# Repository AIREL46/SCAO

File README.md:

# SCAO
Système de Cuisson Assistée par Ordinateur
Ce système est décrit sur le site fablabo http://fablabo.net/wiki/SCAO
Les fichiers de ce projet, au fur et à mesure de l'avancement,  permettent la fabrication des différents sous-ensembles du prototype N°3.

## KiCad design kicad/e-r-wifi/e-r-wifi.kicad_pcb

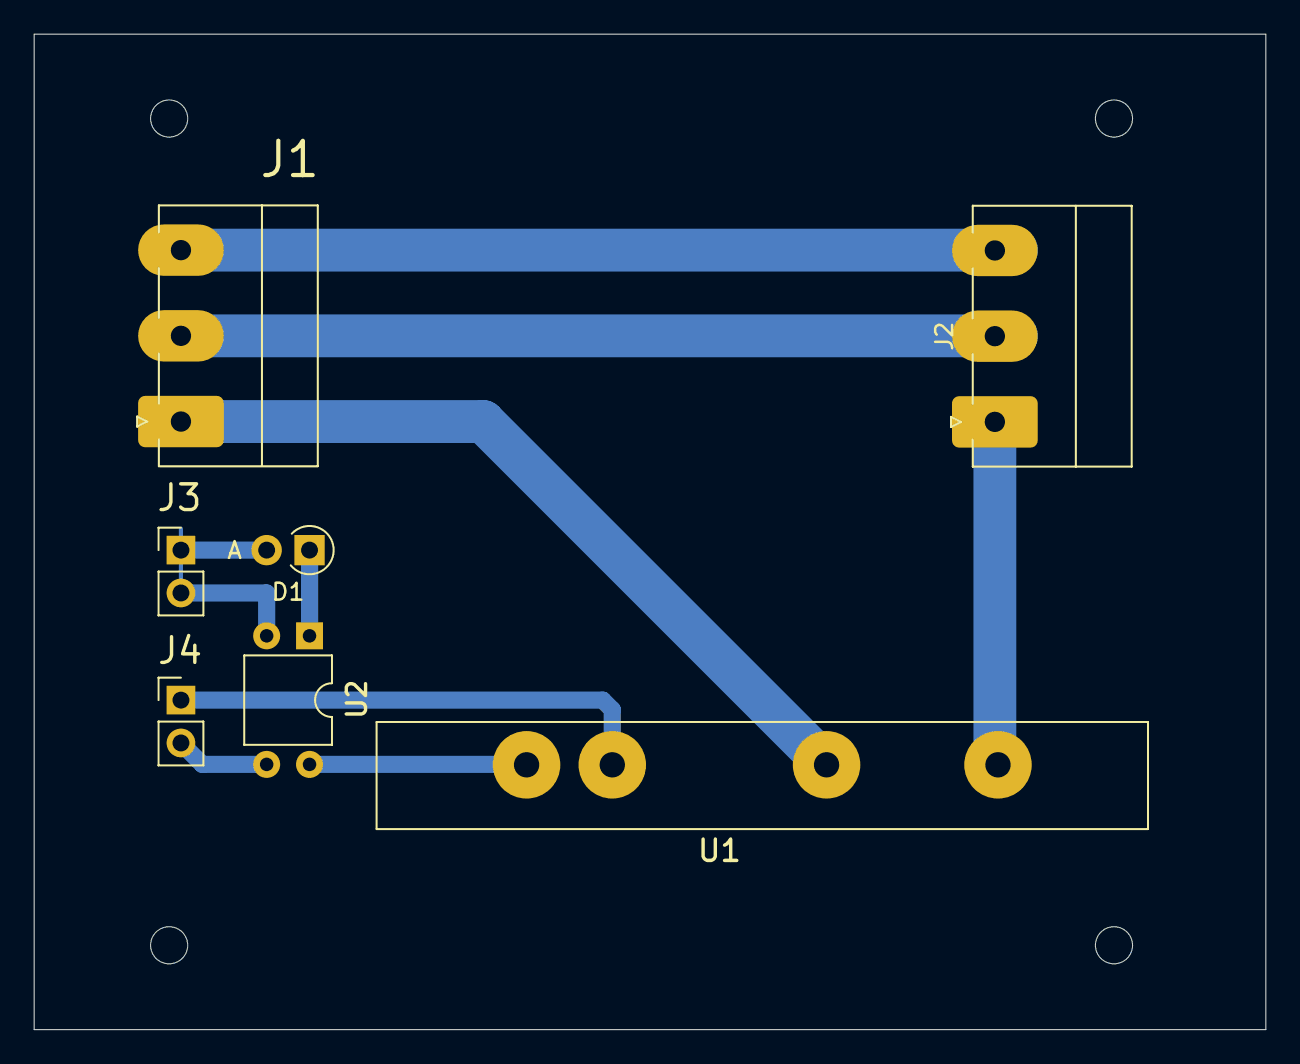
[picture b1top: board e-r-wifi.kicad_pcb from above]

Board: 2 copper layers, 73.0 x 59.0 mm, 7 parts (0 on the bottom side), 9 nets.

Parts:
D1: LED; D_A-405_P2.54mm_Vertical_AnodeUp
J1: Entrée 230V; PhoenixContact_MC_1,5_3-G-5.08_1x03_P5.08mm_Horizontal
J2: Sortie 230V; PhoenixContact_MC_1,5_3-G-5.08_1x03_P5.08mm_Horizontal
J3: cde relais Celduc; PinHeader_1x02_P2.54mm_Vertical
J4: 5V; PinHeader_1x02_P2.54mm_Vertical
U1: SKL10120
U2: PC817; DIP-4_W7.62mm

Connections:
GND: J4.2, U2.3
unnamed: D1.1, U2.1
unnamed: D1.2, J3.1, J3.2, U2.2
unnamed: J1.1, U1.2
unnamed: J1.2, J2.2
unnamed: J1.3, J2.3
unnamed: J2.1, U1.1
unnamed: J4.1, U1.3
unnamed: U1.4, U2.4

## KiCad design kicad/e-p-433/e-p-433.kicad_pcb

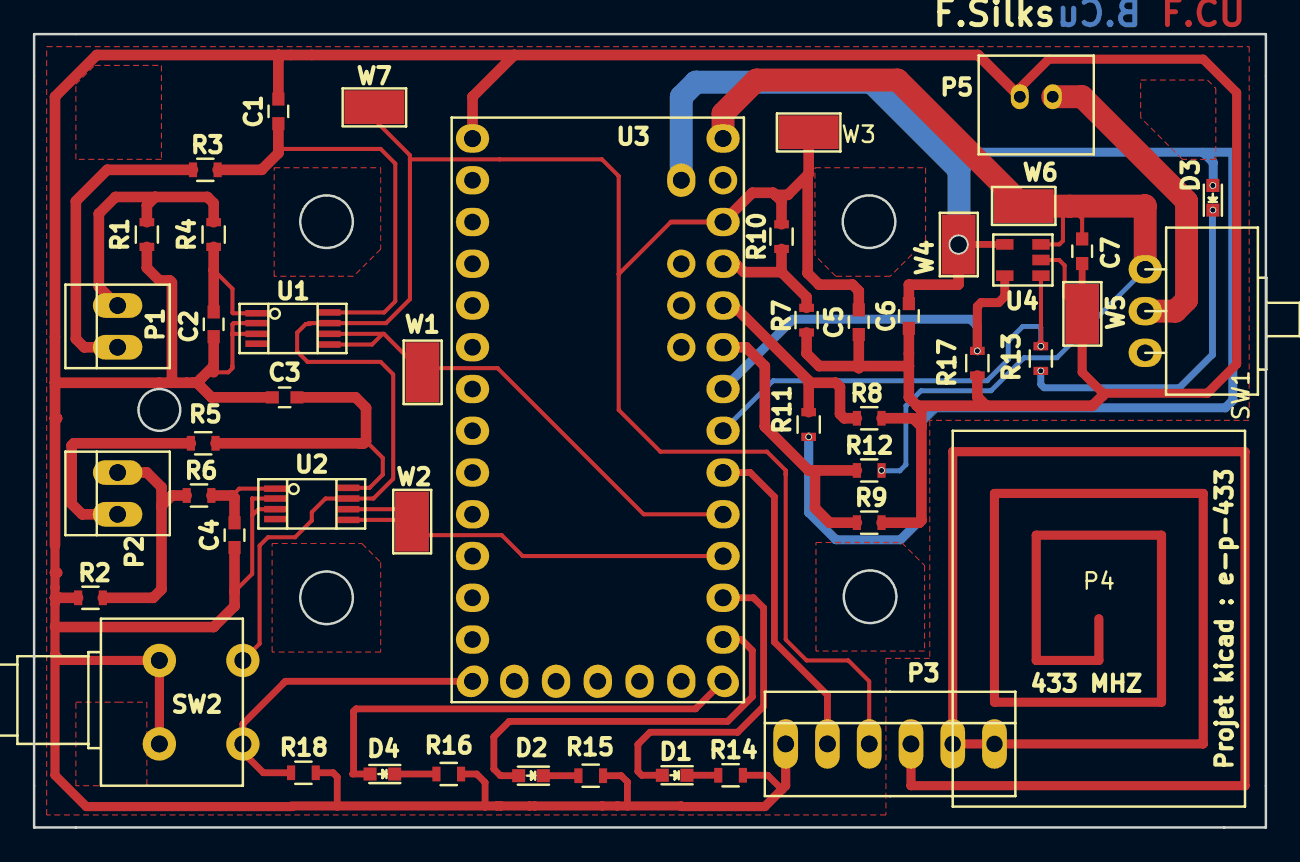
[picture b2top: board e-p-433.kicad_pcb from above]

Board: 2 copper layers, 74.9 x 48.3 mm, 48 parts (0 on the bottom side), 30 nets.

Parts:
C1, C2, C3, C4: 0.1µF; C_0603
C5, C6, C7: 4.7µF; C_0603
D1: Rouge; LED_0603
D2, D3: Jaune; LED_0603
D4: Verte; LED_0603
P1, P2: CONN_01X02; PINHEAD1-2
P3: Transmitter; PINHEAD1-6
P4: ant; Ant
P5: Batterie; con_bat
R1, R2: 1M; R_0603
R3, R4, R5, R6: 10K; R_0603
R7, R8, R9, R10, R11, R12, R17: 4.7K; R_0603
R13: 470; R_0603
R14, R15, R16: 1K; R_0603
R18: 47K; R_0603
SW1: SWITCH_INV; SW_Micro_SPST_Angled
SW2: SW_PUSH_m; SW_Micro_SPST_Angled
SW3: Capuchon vert; Capuchon
U1, U2: AD8495ARMZ; ampli
U3: Teensy_3-2; Teensy_3-1
U4: MCP_73831; SOT23-5
W1: T1; Measurement_Point_Square-SMD-Pad_Big
W2: T2; Measurement_Point_Square-SMD-Pad_Big
W3: 3.3V; Measurement_Point_Square-SMD-Pad_Big
W4: VUSB; Measurement_Point_Square-SMD-Pad_Big
W5: GND; Measurement_Point_Square-SMD-Pad_Big
W6: VBAT; Measurement_Point_Square-SMD-Pad_Big
W7: T3V; Measurement_Point_Square-SMD-Pad_Big

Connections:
3.3V: C5.1, P3.3, R10.2, SW2.1, U1.7, U2.7, U3.3.3V, W3.1, W7.1
+5V: C6.1, D3.2, R11.2, U3.VUSB, U4.4, W4.1
+BATT: C7.1, R12.2, SW1.3, U3.VIN, U4.3, W6.1
GND: C1.1, C2.2, C3.1, C4.2, C5.2, C6.2, C7.2, P3.1, P5.1, R1.2, R2.2, R7.1, R8.1, R9.1, R14.1, R15.1, R16.1, R17.1, R18.2, SW2.3, SW2.4, U1.2, U1.3, U2.2, U2.3, U3.GND, U4.2, W5.1
unnamed: C1.2, R3.1, U1.8
unnamed: C2.1, R4.1, U1.1
unnamed: C3.2, R5.1, U2.8
unnamed: C4.1, R6.1, U2.1
unnamed: D1.1, R14.2
unnamed: D1.2, U3.15
unnamed: D2.1, R15.2
unnamed: D2.2, U3.14
unnamed: D3.1, R13.2
unnamed: D4.1, R16.2
unnamed: D4.2, U3.13
unnamed: P1.1, R3.2
unnamed: P1.2, R1.1, R4.2
unnamed: P2.1, R5.2
unnamed: P2.2, R2.1, R6.2
unnamed: P3.2, U3.18
unnamed: P3.4, P3.5, P3.6, P4.1
unnamed: P5.2, SW1.2
unnamed: R7.2, R10.1, U3.23
unnamed: R8.2, R11.1, U3.22
unnamed: R9.2, R12.1, U3.21
unnamed: R13.1, U3.19, U4.1
unnamed: R17.2, U3.20, U4.5
unnamed: R18.1, SW2.2, U3.12
unnamed: U1.5, U1.6, U3.17, W1.1
unnamed: U2.5, U2.6, U3.16, W2.1

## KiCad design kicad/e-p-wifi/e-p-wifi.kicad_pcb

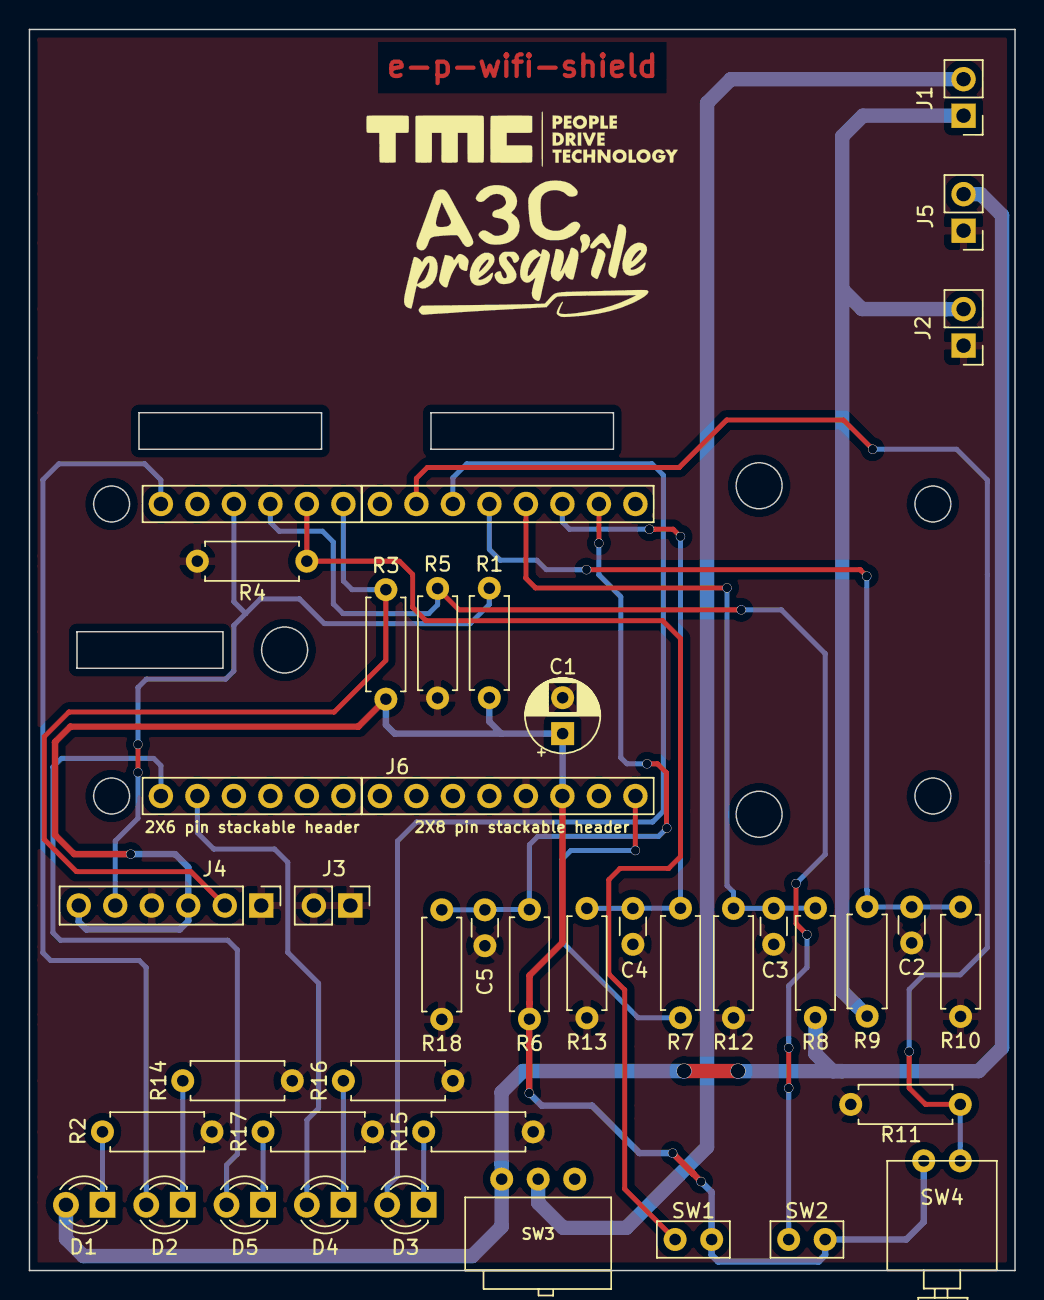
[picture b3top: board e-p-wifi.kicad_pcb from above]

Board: 2 copper layers, 68.6 x 86.4 mm, 38 parts (0 on the bottom side), 24 nets.

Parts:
C1: 4.7µF; CP_Radial_D5.0mm_P2.50mm
C2, C3, C4, C5: 0.1mF; C_Disc_D3.0mm_W1.6mm_P2.50mm
D1: vert; LED_D3.0mm
D2: Vert; LED_D3.0mm
D3: bleu; LED_D3.0mm
D4: Rouge; LED_D3.0mm
D5: Jaune; LED_D3.0mm
J1: Shunt; PinHeader_1x02_P2.54mm_Vertical
J2: Vbat1; PinHeader_1x02_P2.54mm_Vertical
J3: Masse T1; PinHeader_1x02_P2.54mm_Vertical
J4: Température; PinHeader_1x06_P2.54mm_Vertical
J5: Vbat2; PinHeader_1x02_P2.54mm_Vertical
J6: Conn_02x14_MKR1010; PinSocket_2x14_MKR1010
R1, R3, R6, R7, R8, R9, R10, R12, R13, R18: 4.7k; R_Axial_DIN0207_L6.3mm_D2.5mm_P7.62mm_Horizontal
R2, R14, R15, R16, R17: 1K; R_Axial_DIN0207_L6.3mm_D2.5mm_P7.62mm_Horizontal
R4, R5, R11: 47k; R_Axial_DIN0207_L6.3mm_D2.5mm_P7.62mm_Horizontal
SW1: StSp; jumper-switch
SW2: Sleep; jumper-switch
SW3: Conrad 711771; switch
SW4: BP APEM; BP

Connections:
+3V3: C1.1, J4.3, J4.6, J6.+3V3, R1.1, R3.1, R6.1, SW1.1, SW2.1, SW4.1
GND: C1.2, C2.2, C3.2, C4.2, C5.2, J2.1, J3.1, J3.2, J4.1, J4.4, J5.1, J6.GND, R2.1, R4.2, R5.2, R10.2, R11.1, R12.2, R13.2, R14.1, R15.1, R16.1, R17.1, R18.2
unnamed: C2.1, J6.A3, R9.2, R10.1
unnamed: C3.1, J6.A2, R8.2, R12.1
unnamed: C4.1, J6.A1, R7.2, R13.1
unnamed: C5.1, J6.A0, R6.2, R18.1
unnamed: D1.1, R2.2
unnamed: D1.2, J5.2, R8.1, SW3.3
unnamed: D2.1, R14.2
unnamed: D2.2, J6.D5
unnamed: D3.1, R15.2
unnamed: D3.2, J6.A4
unnamed: D4.1, R16.2
unnamed: D4.2, J6.D7
unnamed: D5.1, R17.2
unnamed: D5.2, J6.D6
unnamed: J1.1, J2.2, R9.1
unnamed: J1.2, SW3.2
unnamed: J4.2, J6.D0, R3.2
unnamed: J4.5, J6.D3, R1.2
unnamed: J6.+5V, R7.1
unnamed: J6.A5, R11.2, SW4.2
unnamed: J6.D1, R4.1, SW1.2
unnamed: J6.D2, R5.1, SW2.2

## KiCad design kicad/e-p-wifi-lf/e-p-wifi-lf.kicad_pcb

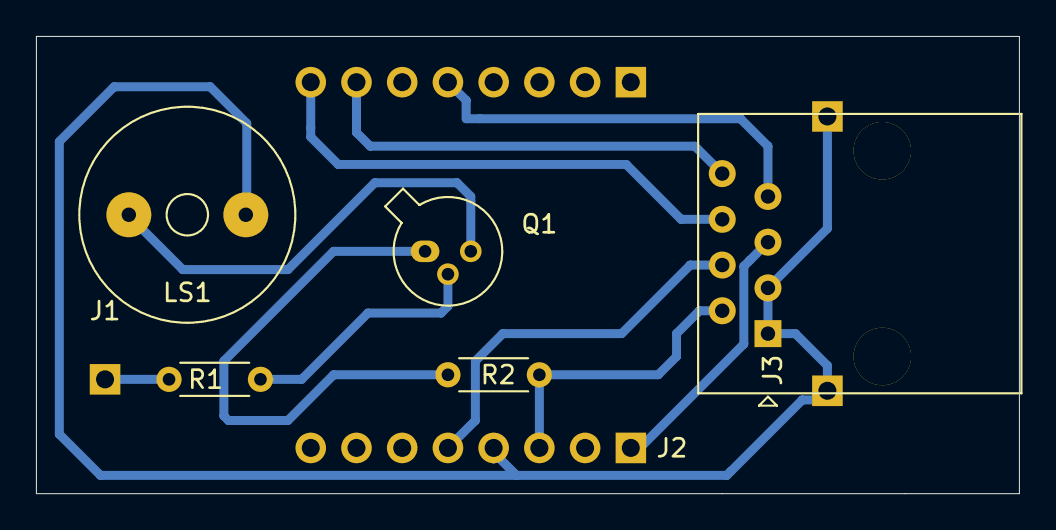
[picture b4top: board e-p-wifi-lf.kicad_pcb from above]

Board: 2 copper layers, 54.6 x 25.4 mm, 7 parts (0 on the bottom side), 11 nets.

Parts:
J1: Speaker; pastille
J2: liaison_filaire; PinHeader_1x08
J3: RJ45
LS1: Device_Speaker; mini_speaker
Q1: 2N2222A; TO-18-3
R1: 470; R_Axial_DIN0204_L3.6mm_D1.6mm_P5.08mm_Horizontal
R2: 0; R_Axial_DIN0204_L3.6mm_D1.6mm_P5.08mm_Horizontal

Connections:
GND: J2.GND, J3.1, J3.3, J3.9, J3.10, LS1.2
unnamed: J1.1, R1.2
unnamed: J2.3.3V, J3.2, R2.2
unnamed: J2.+5V, J3.5
unnamed: J2.A3, J3.7
unnamed: J2.A5, J3.8
unnamed: J2.A6, J3.6
unnamed: J2.Reset, J3.4
unnamed: LS1.1, Q1.3
unnamed: Q1.1, R2.1
unnamed: Q1.2, R1.1

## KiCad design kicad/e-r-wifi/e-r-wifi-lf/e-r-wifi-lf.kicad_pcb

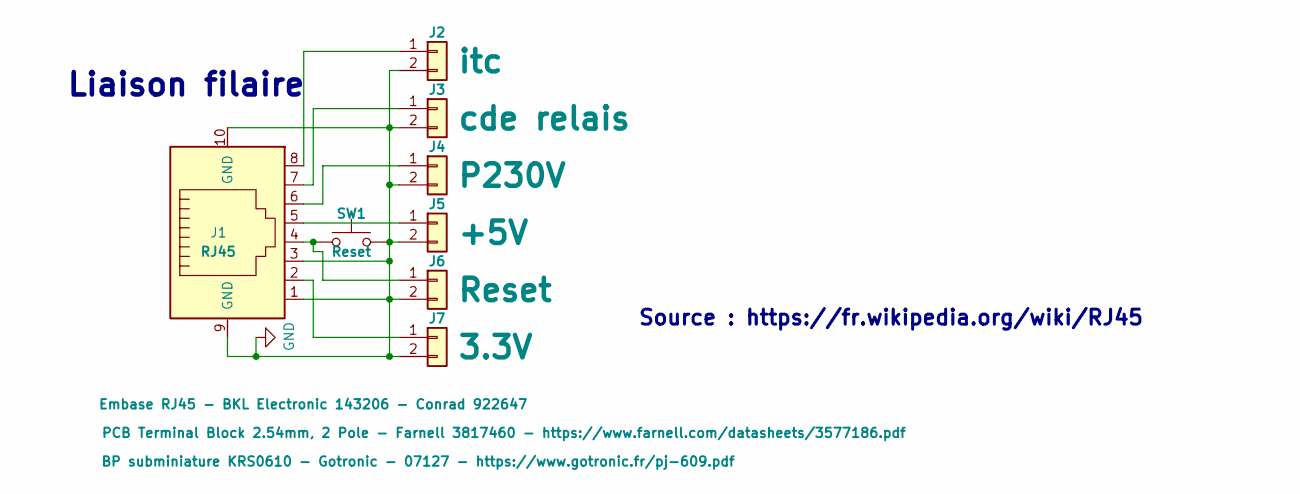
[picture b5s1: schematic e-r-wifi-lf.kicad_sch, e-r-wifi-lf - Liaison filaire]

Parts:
J1: RJ45
J2: itc; PinHeader_1x02_P2.54mm_Vertical
J3: cde relais; PinHeader_1x02_P2.54mm_Vertical
J4: P230V; PinHeader_1x02_P2.54mm_Vertical
J5: +5V; PinHeader_1x02_P2.54mm_Vertical
J6: Reset; PinHeader_1x02_P2.54mm_Vertical
J7: 3.3V; PinHeader_1x02_P2.54mm_Vertical
SW1: Reset; SW_PUSH_6mm

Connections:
GND: J1.1, J1.3, J1.9 (GND), J1.10 (GND), J2.2, J3.2, J4.2, J5.2, J6.2, J7.2, SW1.2
unnamed: J1.2, J7.1
unnamed: J1.4, J6.1, SW1.1
unnamed: J1.5, J5.1
unnamed: J1.6, J4.1
unnamed: J1.7, J3.1
unnamed: J1.8, J2.1

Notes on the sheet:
Source : https://fr.wikipedia.org/wiki/RJ45
Liaison filaire

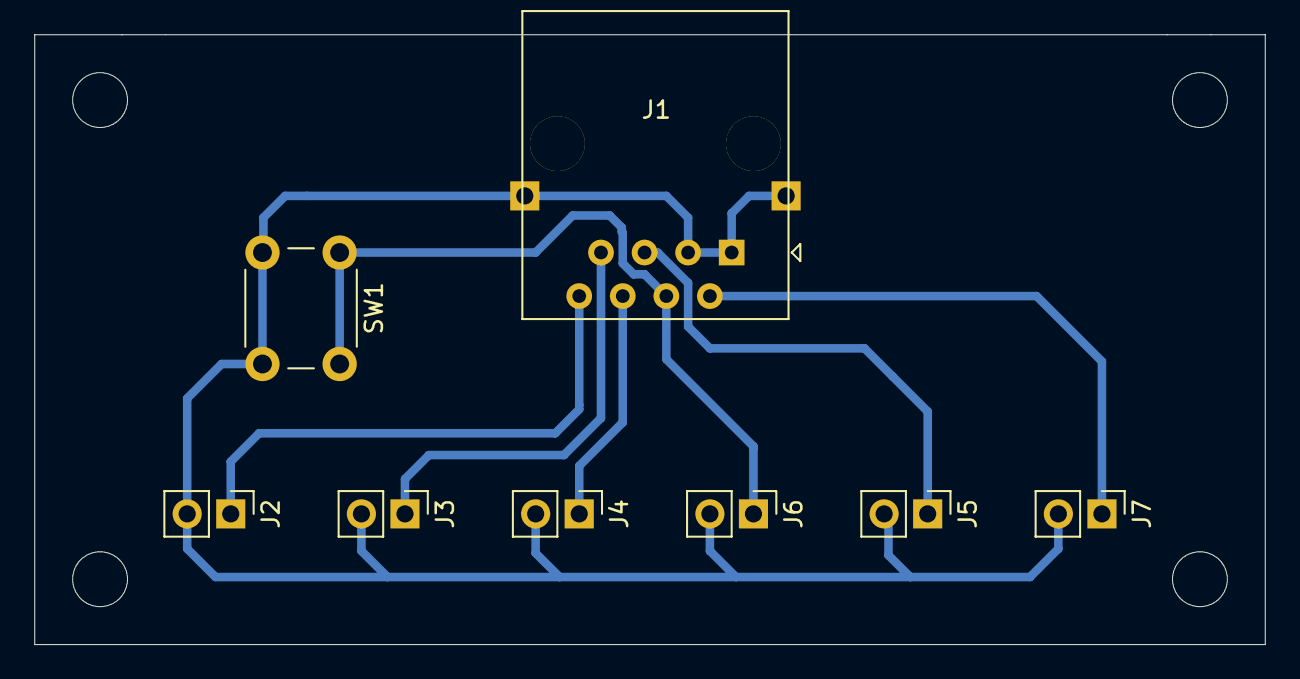
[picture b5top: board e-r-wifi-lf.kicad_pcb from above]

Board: 2 copper layers, 71.8 x 35.6 mm, 8 parts (0 on the bottom side), 7 nets.

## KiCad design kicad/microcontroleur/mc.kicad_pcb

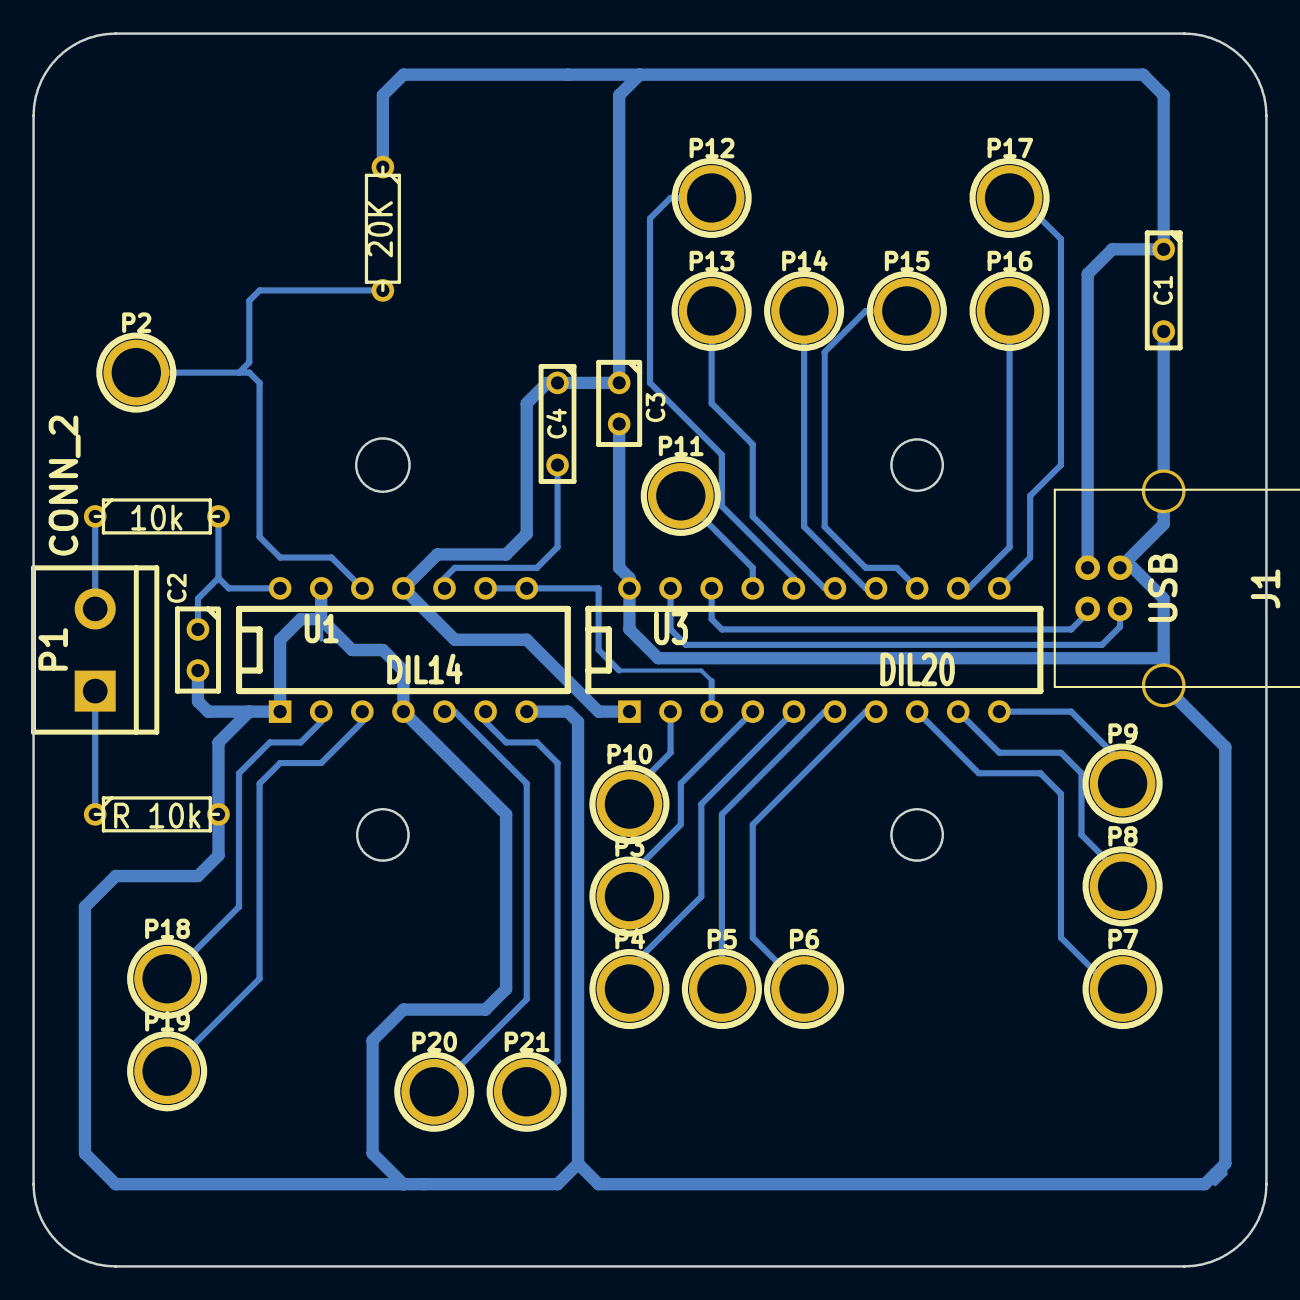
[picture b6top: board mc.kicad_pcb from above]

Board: 2 copper layers, 76.2 x 76.2 mm, 31 parts (0 on the bottom side), 29 nets.

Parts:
C1: 10 microF; C2
C2: C; C1
C3: 0,1 microF; C1
C4: C 10 microF; C2
J1: USB; USB_B
P1: CONN_2; bornier2
P2, P3, P4, P5, P6, P7, P8, P9, P10, P11, P12, P13, P14, P15, P16, P17, P18, P19, P20, P21: CONN_1; 1pin
R1: 20K; R3
R2: R 10k; R3
R3: 10k; R3
U1: DIL14; DIP-14__300
U3: DIL20; DIP-20__300

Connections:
unnamed: J1.2, U3.18
unnamed: J1.3, U3.19
unnamed: P21.1, U1.6
unnamed: P20.1, U1.5
unnamed: P19.1, U1.3
unnamed: P18.1, U1.2
unnamed: C2.1, R3.2, U1.14
unnamed: P1.2, R3.1
unnamed: P10.1, U3.2
unnamed: P1.1, R2.1
unnamed: C4.2, U1.10
unnamed: P2.1, R1.2, U1.12
unnamed: C1.2, C2.2, C3.2, J1.4, J1.5, J1.6, R2.2, U1.1, U1.4, U1.7, U1.13, U3.20
unnamed: P16.1, U3.12
unnamed: U1.8, U1.9, U3.3
unnamed: P3.1, U3.4
unnamed: P4.1, U3.5
unnamed: P5.1, U3.6
unnamed: P6.1, U3.7
unnamed: P7.1, U3.8
unnamed: P8.1, U3.9
unnamed: P9.1, U3.10
unnamed: P17.1, U3.11
unnamed: P15.1, U3.13
unnamed: P14.1, U3.14
unnamed: P13.1, U3.15
unnamed: P12.1, U3.16
unnamed: P11.1, U3.17
unnamed: C1.1, C3.1, C4.1, J1.1, R1.1, U1.11, U3.1

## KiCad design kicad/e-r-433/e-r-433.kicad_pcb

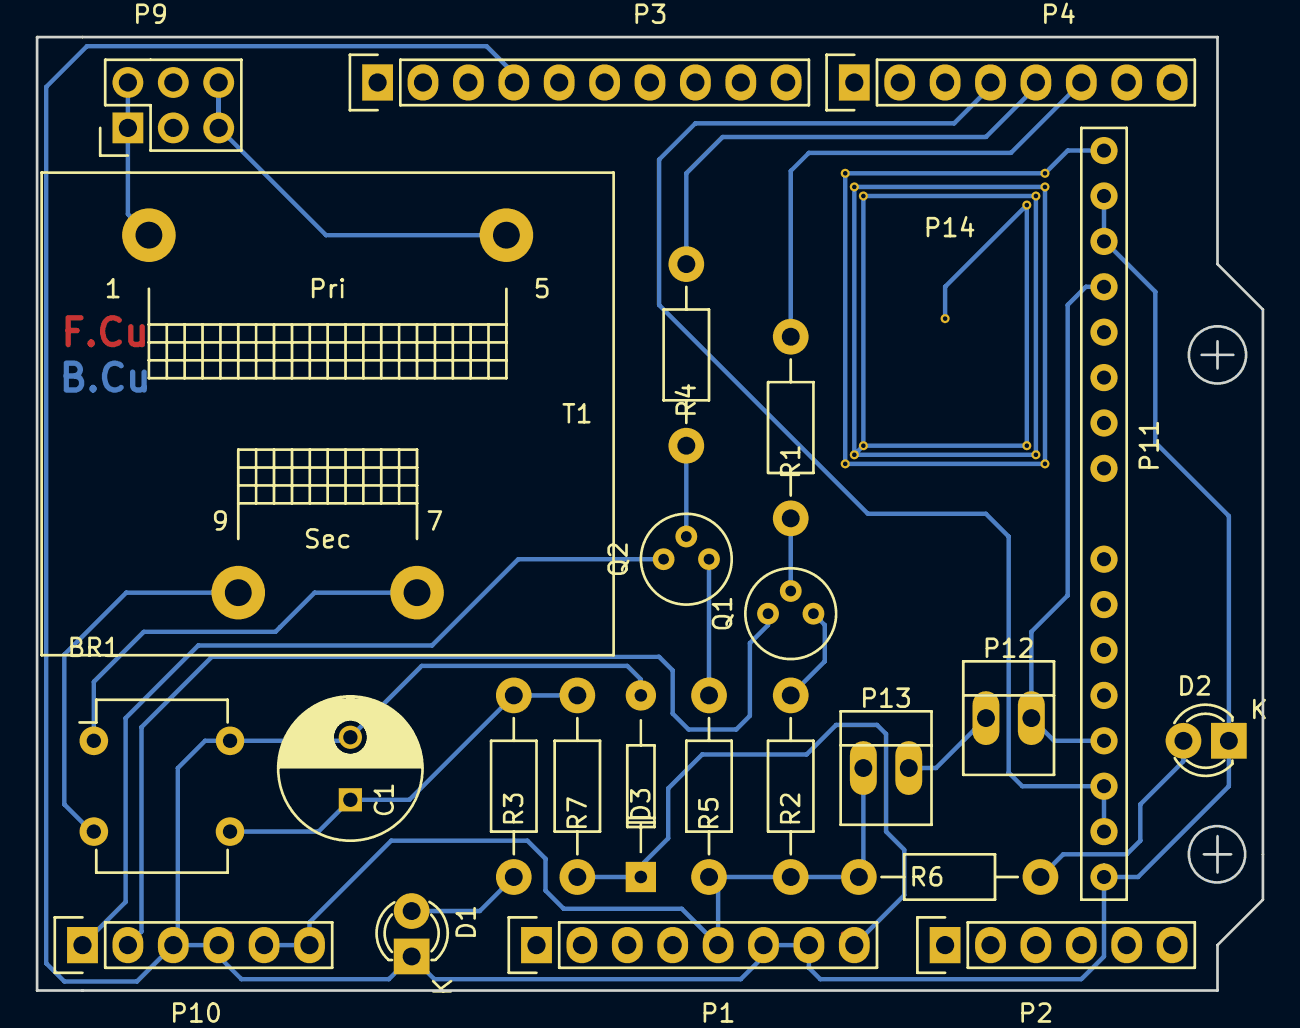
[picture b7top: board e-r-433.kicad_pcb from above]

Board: 2 copper layers, 68.6 x 53.3 mm, 25 parts (0 on the bottom side), 21 nets.

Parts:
BR1: Diotec - B380D; DIP-6_W7.62mm
C1: 100 mF; C_Radial_D8_L11.5_P3.5
D1: Jaune; LED-3MM
D2: Verte; LED-3MM
D3: 12V; Diode_DO-35_SOD27_Horizontal_RM10
P1: Power; Pin_Header_Straight_1x08
P2: Analog; Pin_Header_Straight_1x06
P3: Digital; Pin_Header_Straight_1x10
P4: Digital; Pin_Header_Straight_1x08
P9: 230V; Pin_Header_Straight_2x03
P10: Relay; Pin_Header_Straight_1x06
P11: Receiver-433MHZ; Receiver
P12, P13: 01X02; PINHEAD1-2
P14: Antenne-01X14; Ant
Q1, Q2: 2N2222A; TO-18
R1, R4: 220K; Resistor_Horizontal_RM10mm
R2, R5: 10K; Resistor_Horizontal_RM10mm
R3: 2.2K; Resistor_Horizontal_RM10mm
R6: 1K; Resistor_Horizontal_RM10mm
R7: 47; Resistor_Horizontal_RM10mm
T1: 9V - 1VA; Tr1

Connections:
+5V: P1.5, P10.5, P10.6, P11.4, P11.5, P12.2, P13.1, R2.1, R5.1, R6.1
/2: P4.6, R1.2
/3(**): P4.5, R4.2
/4: P4.4, P11.6, P11.7
/Ant: P11.1, P14.1, P14.2, P14.3, P14.4, P14.5, P14.6, P14.7, P14.8, P14.9, P14.10, P14.11, P14.12, P14.13, P14.14
/Control-0: P10.1, Q2.3
/Control-1: P10.2, Q1.3
/Vin: D3.1, P1.8, R7.2
GND: BR1.4, C1.2, D1.1, D2.1, D3.2, P1.6, P1.7, P3.4, P10.3, P10.4, P11.2, P11.3, P11.8
unnamed: BR1.1, T1.4
unnamed: BR1.2, T1.3
unnamed: BR1.3, C1.1, R3.1, R7.1
unnamed: D1.2, R3.2
unnamed: D2.2, R6.2
unnamed: P9.1, P9.2, T1.1
unnamed: P9.5, P9.6, T1.2
unnamed: P12.1, P13.2
unnamed: Q1.1, R2.2
unnamed: Q1.2, R1.1
unnamed: Q2.1, R5.2
unnamed: Q2.2, R4.1

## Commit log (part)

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2020-04-23 Ajout de photos e-p-wifi
2020-04-24 Photos e-p-wifi
2020-04-26 Ajout du CR de Clément
2020-04-27 Ajout Firewall gufw
2020-05-01 mise à jour kicad
2020-05-01 Devis Eurocircuits
2020-05-03 Mise à jour du 03/05/2020
2020-05-05 Création du répertoire SCAO/Ping/openscad/willy
2020-05-05 Modification de top.png
2020-05-08 Mise à jour du 08/05/2020
2020-05-11 Ajout du fp-lib-table au projet shield Kicad
2020-05-16 Ajout de la photo du shield_a
2020-05-20 Mise à jour du 20 mai 2020
2020-05-20 Ajout de la procédure de test
2020-05-20 Mise à jour de la procédure de test
2020-05-25 Mise à jour 25/05/2020
2020-06-07 Mise à jour du 07/06/2020
2020-06-07 Modification de e-p-wifi.ino
2020-06-21 Maj association
2020-06-23 Ajout de fichiers dans rep e-p-wifi
2020-06-26 Mise à jour
2020-07-02 Evolution de e-p-wifi
2020-07-11 Evolution e-p-wifi
2020-07-11 Evolution A3CP
2020-07-13 Reconnaissance d'intérêt général
2020-07-21 Création de annexe.pdf
2020-07-27 Rectificatif de la note de frais de Marie Sarah Laroche
2020-09-18 Création du dossier de presse
2020-09-18 transfert des fichiers du site Web -> association/com/site-web
2020-10-23 Création de l'interface Celduc
2020-10-26 Mise à jour des adhésions
2021-07-17 mise à jour Olivier
2021-07-17 Mise à jour Régis
2023-04-11 Mise à jour de Régis
2025-07-08 Revert suppression
2025-07-09 Ajout du répertoire atelier_logiciel
2025-07-09 Ajout des photos de St Jacut
2025-07-13 Ajout de 2 photos
2025-07-16 Ajout de 2 photos de la sculpture les mangeurs de pdt
2025-07-17 Ajout de la photo métier à tisser
2025-07-20 Ajouter trois photos de Nuenen
2025-07-23 Ajout de photos Eindhoven
2025-07-23 Correction faute de frappe
2025-07-23 Correction orthographique
2025-07-25 Ajout de photo Eindhoven
2025-07-26 Ajout de la photo du carrelage du terminus Nord
2025-09-14 Ajout des cartes des parcs nationaux du Brabant
2025-09-22 voyage à Tilburg
2025-10-11 Ajout des photos de Tilburg
2025-10-13 Ajout photo
2025-11-01 Ajouts généalogie
2025-11-05 Ajout des photos d'Andalousie
2025-11-11 Ajout de la carte Séville-Huelva-Cadix
2025-11-15 Ajout de 2 cartes
2025-11-19 Ajout de la carte de Cadix
2025-11-26 Ajout de 2 photos Mosquée-Cathédrale de Cordsoue
2025-11-27 Ajout mosquee_cathedrale_1.png
2025-11-28 Ajout mosquee_cathedrale_2.png
2025-11-28 Ajout memoires_a5_4.epub
2025-12-08 Modification de mosquee_cathedrale_2.png
2026-01-09 Ajout du fichier de test speaker
2026-01-09 Modification des fichiers SCAO/Ping/LibreCAD/MKR1010-shield
2026-01-09 Ajout des fichiers implantation TOP fournis par Atexa électronique
2026-01-20 ajout et modifications de fichiers
2026-01-24 Préparation des fichiers pour la cde LNA
2026-01-24 Préparation des fichiers de le cde LNA
2026-02-07 Ajout de fichiers
2026-02-11 Ajout carnac_jolie_fille
2026-02-11 Modification des fichiers test
2026-02-12 Modification du fichier top.stl avant commande chez LNA
2026-03-04 ajout du répertoire SCAO/Arduino/e-p-filaire
2026-04-13 Ajout de la photo du tournesol bébé
2026-06-19 Ajout page d'accueil GitHub Pages
2026-06-20 Ajout index.html de test
2026-06-20 Suppression du fichier index.md
2026-06-20 Fix GitHub Pages (disable Jekyll)
2026-06-20 Pages debug test
2026-06-20 Enable GitHub Pages via Actions
2026-06-20 Remove broken submodule git/SCAO
2026-06-22 Build wiki automatique
2026-06-22 Fix index generation (env vars)
2026-06-22 Remove broken git/demo causing Pages failure
2026-06-22 Deploy Pages depuis docs
2026-06-23 Ajout du style CSS
2026-06-23 Modification du style CSS
2026-06-23 Fix GitHub Pages CSS path
2026-06-23 Modification du fichier scao.css
2026-06-23 suppression du fichier docs/css/scao.css
2026-06-25 test final pages
2026-06-25 fix background color override
2026-06-25 move css into docs for github pages
2026-06-26 modification max-with
2026-06-26 modification max-with 160ch
2026-06-26 Fond beige
2026-06-26 ch rouge
2026-06-26 auto
2026-06-26 Car bleu
2026-06-26 modif fond
2026-06-27 Move CSS to published root
2026-06-27 lien css
2026-06-27 adresse des photos
2026-06-28 Suppression des fichiers plan de management obsolètes
2026-06-28 Suppression des répertoires AGIR et AICO
2026-06-28 move site to root for GitHub Pages
2026-06-29 Mise à jour de atelier_vt_c_v_otterlo

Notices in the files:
kicad/e-r-wifi/e-r-wifi.kicad_pcb:
CC-BY
